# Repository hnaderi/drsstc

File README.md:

# DRSSTC

This is a work in progress...

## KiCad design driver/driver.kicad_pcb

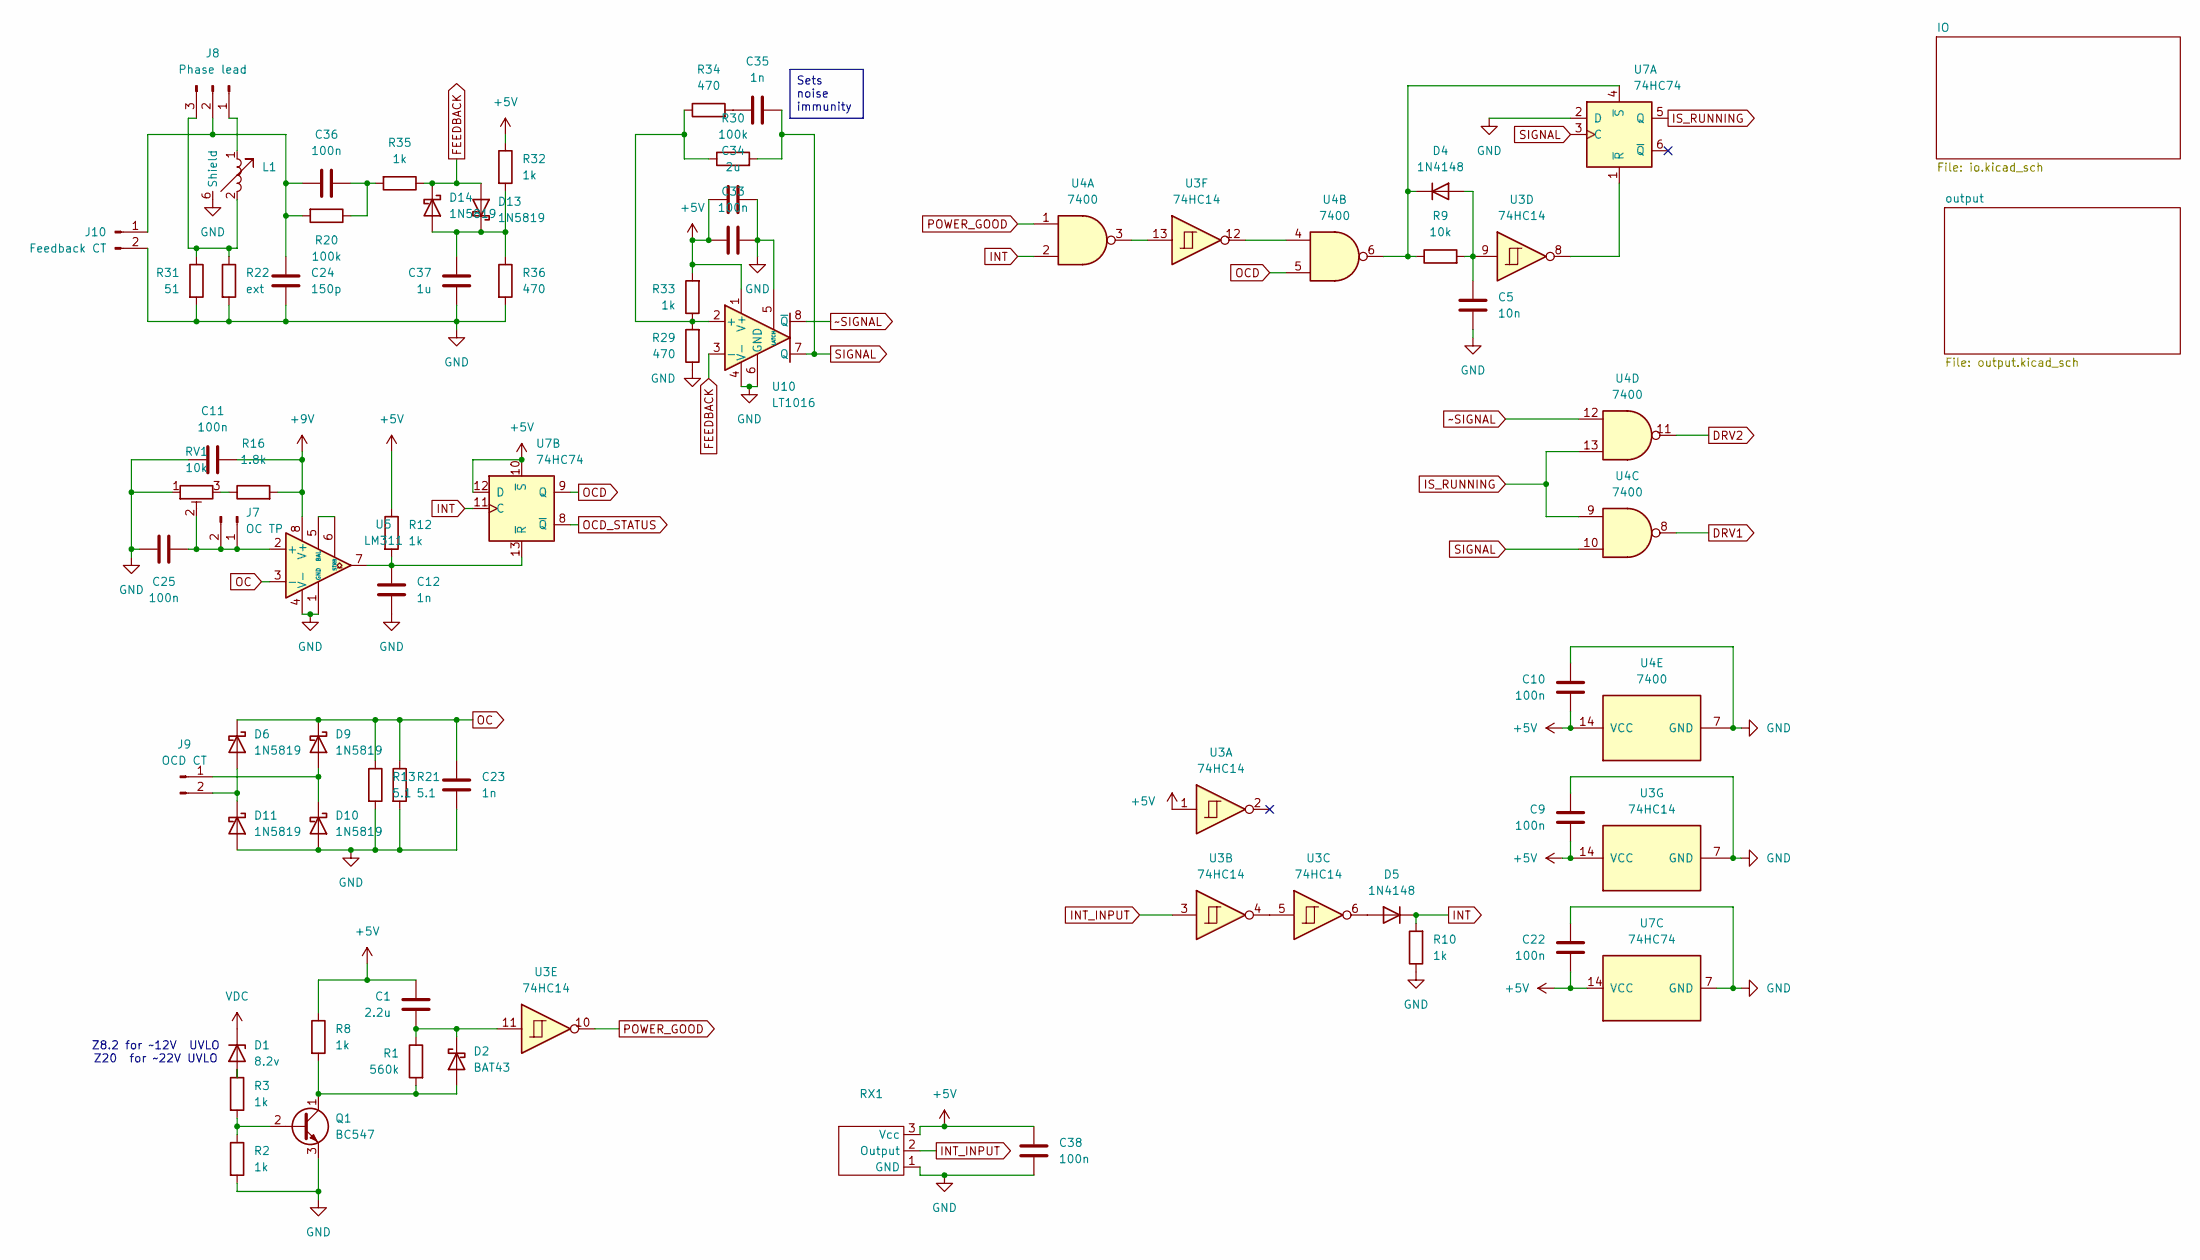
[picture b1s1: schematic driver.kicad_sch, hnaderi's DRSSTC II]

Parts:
C1: 2.2u; C_Disc_D4.7mm_W2.5mm_P5.00mm
C5: 10n; C_Disc_D4.7mm_W2.5mm_P5.00mm
C9, C10, C11, C22, C25, C33, C36, C38: 100n; C_Disc_D4.7mm_W2.5mm_P5.00mm
C12, C23, C35: 1n; C_Disc_D4.7mm_W2.5mm_P5.00mm
C24: 150p; C_Disc_D4.7mm_W2.5mm_P5.00mm
C34: 2u; C_Rect_L7.2mm_W7.2mm_P5.00mm_FKS2_FKP2_MKS2_MKP2
C37: 1u; C_Disc_D4.7mm_W2.5mm_P5.00mm
D1: 8.2v; D_DO-35_SOD27_P2.54mm_Vertical_KathodeUp
D2: BAT43; D_DO-35_SOD27_P2.54mm_Vertical_KathodeUp
D4, D5: 1N4148; D_DO-35_SOD27_P2.54mm_Vertical_KathodeUp
D6, D9, D10, D11, D13, D14: 1N5819; D_DO-41_SOD81_P2.54mm_Vertical_KathodeUp
J7: OC TP; PinHeader_1x02_P2.54mm_Vertical
J8: Phase lead; PinHeader_1x03_P2.54mm_Vertical
J9: OCD CT; JST_XH_B2B-XH-A_1x02_P2.50mm_Vertical
J10: Feedback CT; JST_XH_B2B-XH-A_1x02_P2.50mm_Vertical
L1: universal tunable inductor
Q1: BC547; TO-92_Inline_Wide
R1: 560k; R_Axial_DIN0207_L6.3mm_D2.5mm_P2.54mm_Vertical
R2, R3, R8, R10, R12, R32, R33: 1k; R_Axial_DIN0207_L6.3mm_D2.5mm_P2.54mm_Vertical
R9: 10k; R_Axial_DIN0207_L6.3mm_D2.5mm_P2.54mm_Vertical
R13, R21: 5.1; R_Axial_DIN0207_L6.3mm_D2.5mm_P2.54mm_Vertical
R16: 1.8k; R_Axial_DIN0207_L6.3mm_D2.5mm_P2.54mm_Vertical
R20: 100k; R_Axial_DIN0309_L9.0mm_D3.2mm_P2.54mm_Vertical
R22: ext; R_Axial_DIN0309_L9.0mm_D3.2mm_P2.54mm_Vertical
R29, R34, R36: 470; R_Axial_DIN0207_L6.3mm_D2.5mm_P2.54mm_Vertical
R30: 100k; R_Axial_DIN0207_L6.3mm_D2.5mm_P2.54mm_Vertical
R31: 51; R_Axial_DIN0309_L9.0mm_D3.2mm_P2.54mm_Vertical
R35: 1k; R_Axial_DIN0309_L9.0mm_D3.2mm_P2.54mm_Vertical
RV1: 10k; Potentiometer_Bourns_3296W_Vertical
RX1: hnaderi-opl530-rx
U3: 74HC14; DIP-14_W7.62mm
U4: 7400; DIP-14_W7.62mm
U5: LM311; DIP-8_W7.62mm
U7: 74HC74; DIP-14_W7.62mm
U10: LT1016; DIP-8_W7.62mm

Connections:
+5V: C1.2, C9.2, C10.2, C22.2, C33.2, C34.2, C38.1, R8.1, R12.1, R32.1, R33.2, RX1.3 (Vcc), U3.1, U3.14 (VCC), U4.14 (VCC), U7.10 (~S), U7.12 (D), U7.14 (VCC), U10.1 (V+); also elsewhere on the board
+9V: C11.2, R16.2, U5.8 (V+); also elsewhere on the board
DRV1: U4.8; also elsewhere on the board
DRV2: U4.11; also elsewhere on the board
FEEDBACK: D13.2 (A), D14.1 (K), R35.1, U10.3 (-); also elsewhere on the board
GND: C5.2, C9.1, C10.1, C11.1, C12.2, C22.1, C23.2, C24.1, C25.1, C33.1, C34.1, C37.2, C38.2, D10.2 (A), D11.2 (A), J10.2, L1.6 (Shield), Q1.3 (E), R2.2, R10.1, R13.2, R21.2, R22.2, R29.1, R31.2, R36.2, RV1.1, RX1.1 (GND), U3.7 (GND), U4.7 (GND), U5.1 (GND), U5.4 (V-), U7.2 (D), U7.7 (GND), U10.4 (V-), U10.5 (LATCH), U10.6 (GND); also elsewhere on the board
INT: D5.1 (K), R10.2, U4.2, U7.11 (C); also elsewhere on the board
INT_INPUT: RX1.2 (Output), U3.3; also elsewhere on the board
IS_RUNNING: U4.9, U4.13, U7.5 (Q)
unnamed: C35.2, R34.2
unnamed: C36.1, R20.1, R35.2
unnamed: D1.2 (A), R3.1
unnamed: D2.2 (A), Q1.1 (C), R1.2, R8.2
unnamed: C1.1, D2.1 (K), R1.1, U3.11
unnamed: C5.1, D4.2 (A), R9.2, U3.9
unnamed: D4.1 (K), R9.1, U4.6, U7.4 (~S)
unnamed: D5.2 (A), U3.6
unnamed: D9.2 (A), D10.1 (K), J9.1
unnamed: D6.2 (A), D11.1 (K), J9.2
unnamed: C37.1, D13.1 (K), D14.2 (A), R32.2, R36.1
unnamed: C25.2, J7.1, J7.2, RV1.2, U5.2 (+)
unnamed: J8.1, L1.1
unnamed: J8.3, L1.2, R22.1, R31.1
unnamed: C24.2, C36.2, J8.2, J10.1, R20.2
unnamed: Q1.2 (B), R2.1, R3.2
unnamed: R16.1, RV1.3
unnamed: U3.4, U3.5
unnamed: U3.12, U4.4
unnamed: U3.13, U4.3
unnamed: U5.5 (BAL), U5.6 (STRB)
unnamed: U3.8, U7.1 (~R)
unnamed: C12.1, R12.2, U5.7, U7.13 (~R)
unnamed: R29.2, R30.1, R33.1, R34.1, U10.2 (+)
OC: C23.1, D6.1 (K), D9.1 (K), R13.1, R21.1, U5.3 (-)
OCD: U4.5, U7.9 (Q)
OCD_STATUS: U7.8 (~Q); also elsewhere on the board
POWER_GOOD: U3.10, U4.1; also elsewhere on the board
SIGNAL: C35.1, R30.2, U4.10, U7.3 (C), U10.7 (Q); also elsewhere on the board
VDC: D1.1 (K); also elsewhere on the board
~SIGNAL: U4.12, U10.8 (~Q)

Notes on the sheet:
Z8.2 for ~12V UVLO Z20 for ~22V UVLO
Sets noise immunity

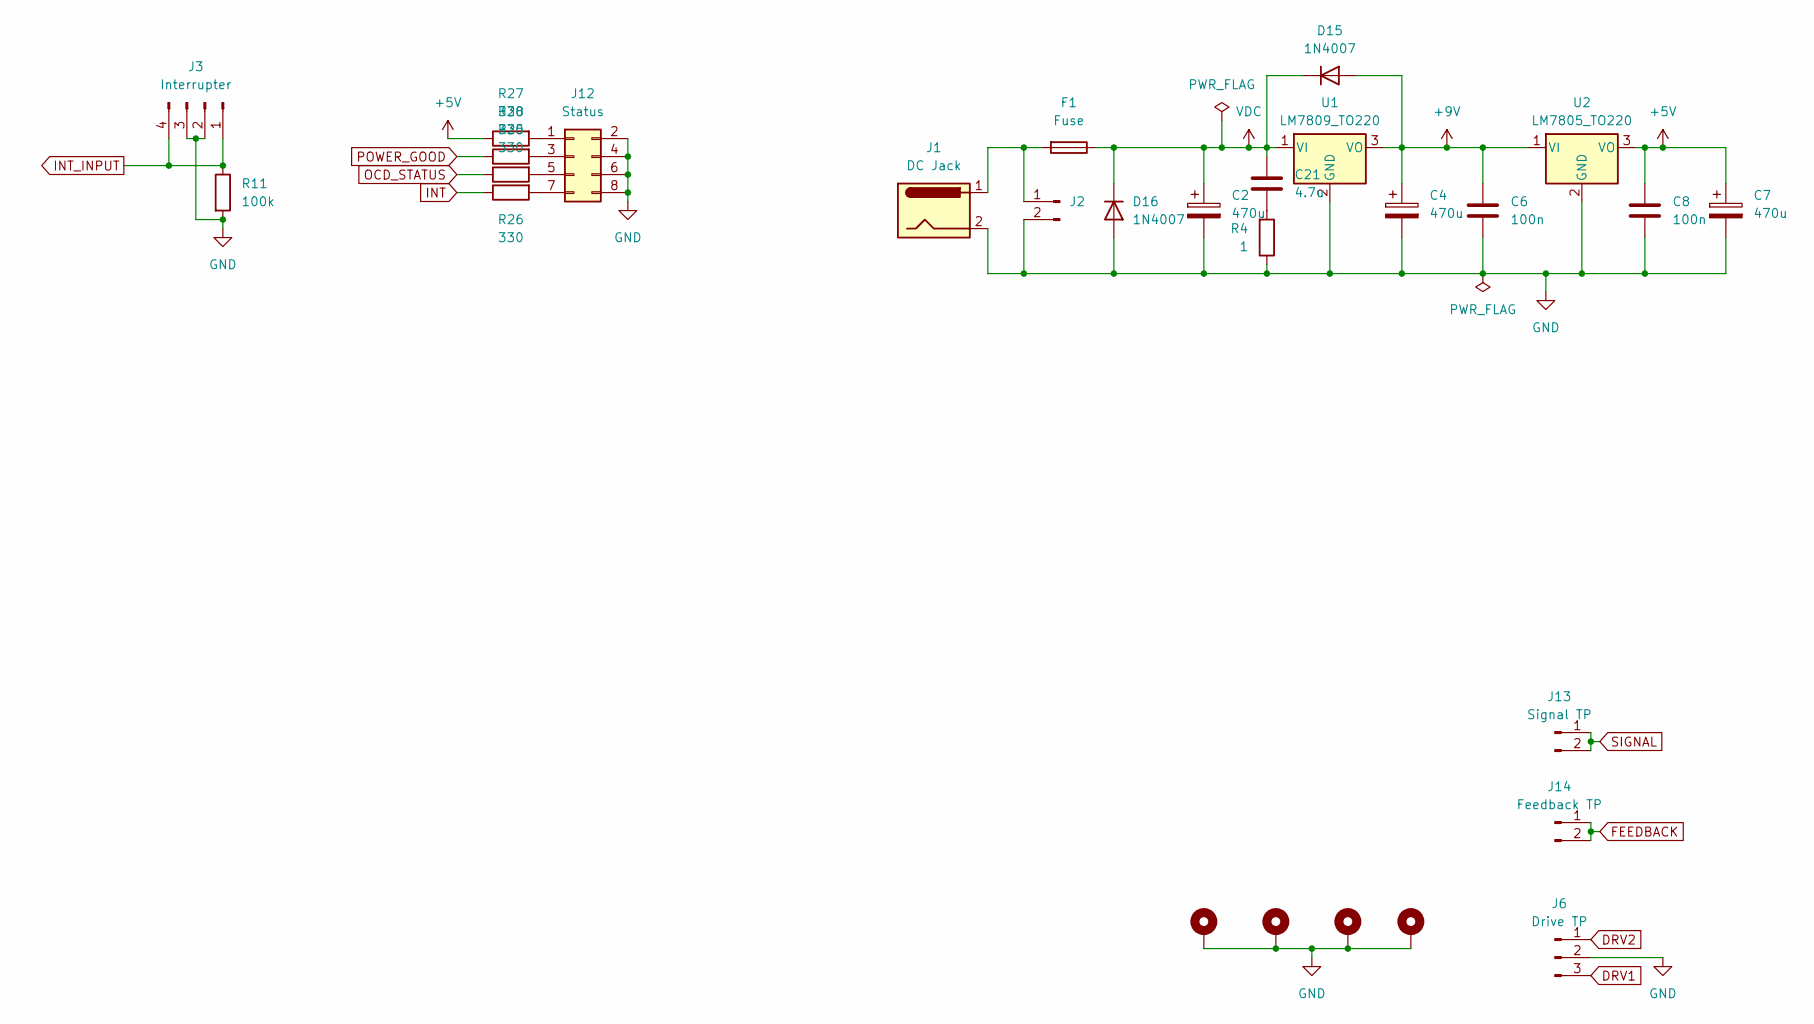
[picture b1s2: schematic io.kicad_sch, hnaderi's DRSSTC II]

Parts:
C2, C4, C7: 470u; CP_Radial_D10.0mm_P5.00mm
C6, C8: 100n; C_Disc_D4.7mm_W2.5mm_P5.00mm
C21: 4.7u; C_Disc_D4.7mm_W2.5mm_P5.00mm
D15, D16: 1N4007; D_DO-35_SOD27_P2.54mm_Vertical_KathodeUp
F1: Fuse; Fuse_Littelfuse_395Series
H1, H2, H3, H4: Body; MountingHole_3.2mm_M3_DIN965_Pad_TopBottom
J1: DC Jack; BarrelJack_Horizontal
J2: JST_XH_B2B-XH-A_1x02_P2.50mm_Vertical
J3: Interrupter; PinHeader_1x04_P2.54mm_Vertical
J6: Drive TP; PinHeader_1x03_P2.54mm_Vertical
J12: Status; PinHeader_2x04_P2.54mm_Vertical
J13: Signal TP; PinHeader_1x02_P2.54mm_Vertical
J14: Feedback TP; PinHeader_1x02_P2.54mm_Vertical
R4: 1; R_Axial_DIN0207_L6.3mm_D2.5mm_P2.54mm_Vertical
R11: 100k; R_Axial_DIN0207_L6.3mm_D2.5mm_P2.54mm_Vertical
R25, R26, R27, R28: 330; R_Axial_DIN0207_L6.3mm_D2.5mm_P2.54mm_Vertical
U1: LM7809_TO220; TO-220-3_Vertical
U2: LM7805_TO220; TO-220-3_Vertical

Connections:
+5V: C7.1, C8.1, R27.1, U2.3 (VO); also elsewhere on the board
+9V: C4.1, C6.1, D15.2 (A), U1.3 (VO), U2.1 (VI); also elsewhere on the board
DRV1: J6.3; also elsewhere on the board
DRV2: J6.1; also elsewhere on the board
FEEDBACK: J14.1, J14.2; also elsewhere on the board
GND: C2.2, C4.2, C6.2, C7.2, C8.2, D16.2 (A), H1.1, H2.1, H3.1, H4.1, J1.2, J2.2, J3.2, J3.3, J6.2, J12.2, J12.4, J12.6, J12.8, R4.1, R11.2, U1.2 (GND), U2.2 (GND); also elsewhere on the board
INT: R26.1; also elsewhere on the board
INT_INPUT: J3.1, J3.4, R11.1; also elsewhere on the board
unnamed: C21.2, R4.2
unnamed: F1.2, J1.1, J2.1
unnamed: J12.1, R27.2
unnamed: J12.3, R28.2
unnamed: J12.5, R25.2
unnamed: J12.7, R26.2
OCD_STATUS: R25.1; also elsewhere on the board
POWER_GOOD: R28.1; also elsewhere on the board
SIGNAL: J13.1, J13.2; also elsewhere on the board
VDC: C2.1, C21.1, D15.1 (K), D16.1 (K), F1.1, U1.1 (VI); also elsewhere on the board

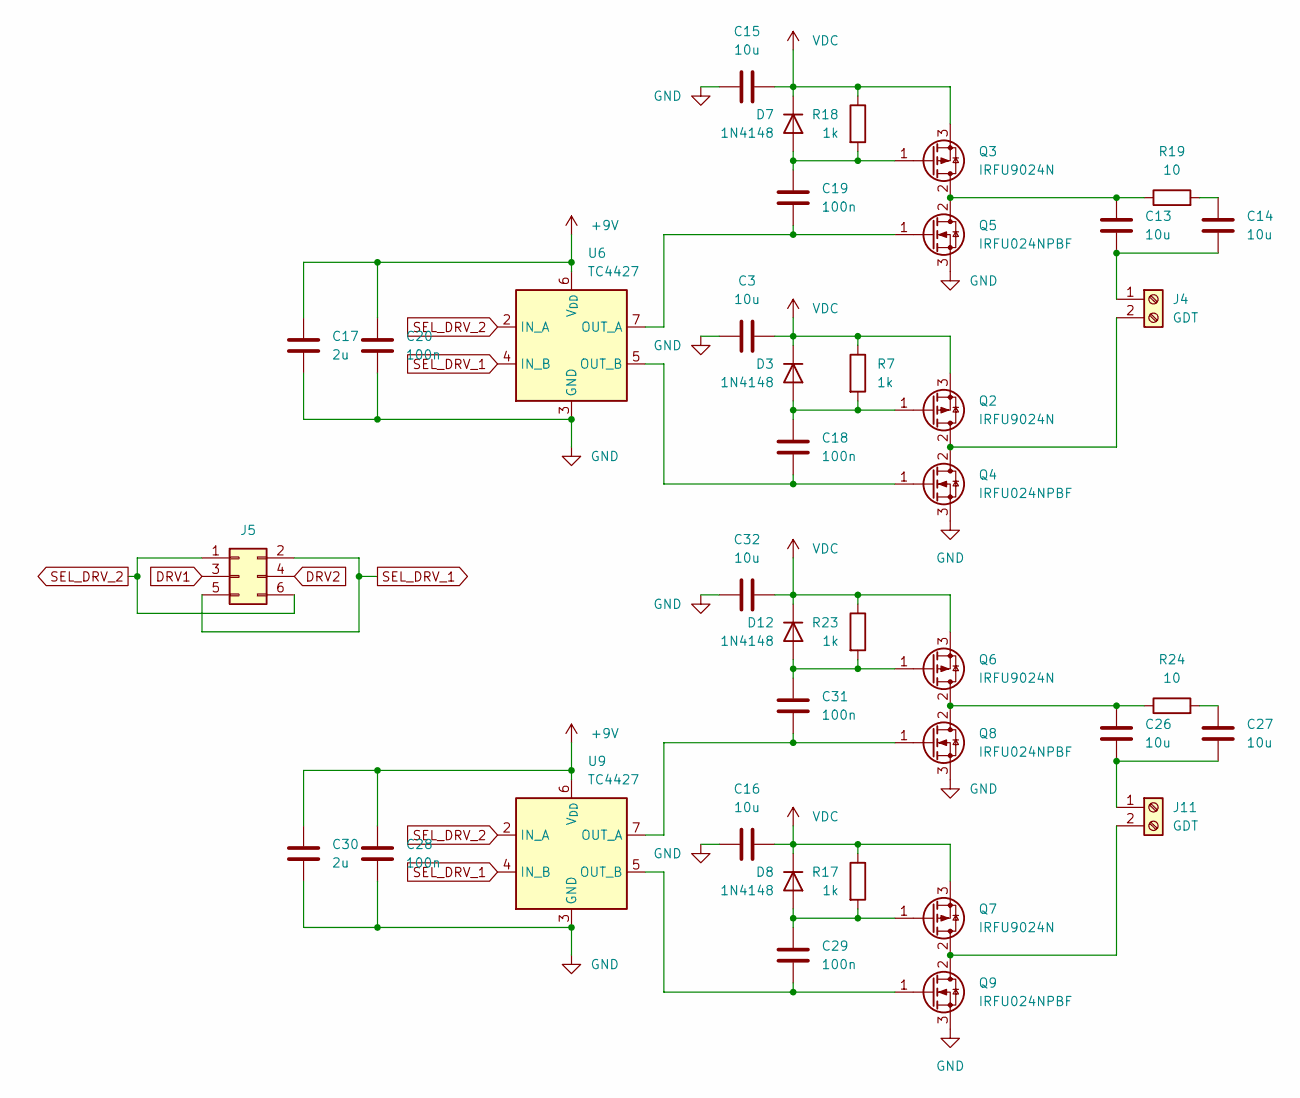
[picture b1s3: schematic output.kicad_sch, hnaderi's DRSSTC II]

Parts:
C3, C13, C14, C15, C16, C26, C27, C32: 10u; C_Disc_D4.7mm_W2.5mm_P5.00mm
C17, C30: 2u; C_Rect_L7.2mm_W7.2mm_P5.00mm_FKS2_FKP2_MKS2_MKP2
C18, C19, C20, C28, C29, C31: 100n; C_Disc_D4.7mm_W2.5mm_P5.00mm
D3, D7, D8, D12: 1N4148; D_DO-35_SOD27_P2.54mm_Vertical_KathodeUp
J4, J11: GDT; JST_XH_B2B-XH-A_1x02_P2.50mm_Vertical
J5: Conn_02x03_Odd_Even; PinHeader_2x03_P2.54mm_Vertical
Q2, Q3, Q6, Q7: IRFU9024N; TO-251-3-1EP_Horizontal_TabDown
Q4, Q5, Q8, Q9: IRFU024NPBF; TO-251-3-1EP_Horizontal_TabDown
R7, R17, R18, R23: 1k; R_Axial_DIN0207_L6.3mm_D2.5mm_P2.54mm_Vertical
R19, R24: 10; R_Axial_DIN0309_L9.0mm_D3.2mm_P2.54mm_Vertical
U6, U9: TC4427; DIP-8_W7.62mm

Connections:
+9V: C17.2, C20.2, C28.2, C30.2, U6.6 (V_{DD}), U9.6 (V_{DD}); also elsewhere on the board
DRV1: J5.3; also elsewhere on the board
DRV2: J5.4; also elsewhere on the board
GND: C3.2, C15.2, C16.2, C17.1, C20.1, C28.1, C30.1, C32.2, Q4.3 (S), Q5.3 (S), Q8.3 (S), Q9.3 (S), U6.3 (GND), U9.3 (GND); also elsewhere on the board
unnamed: C14.1, R19.2
unnamed: C27.1, R24.2
unnamed: C18.1, D3.2 (A), Q2.1 (G), R7.2
unnamed: C19.1, D7.2 (A), Q3.1 (G), R18.2
unnamed: C29.1, D8.2 (A), Q7.1 (G), R17.2
unnamed: C31.1, D12.2 (A), Q6.1 (G), R23.2
unnamed: C13.2, C14.2, J4.1
unnamed: J4.2, Q2.2 (D), Q4.2 (D)
unnamed: C26.2, C27.2, J11.1
unnamed: J11.2, Q7.2 (D), Q9.2 (D)
unnamed: C13.1, Q3.2 (D), Q5.2 (D), R19.1
unnamed: C18.2, Q4.1 (G), U6.5 (OUT_B)
unnamed: C19.2, Q5.1 (G), U6.7 (OUT_A)
unnamed: C26.1, Q6.2 (D), Q8.2 (D), R24.1
unnamed: C31.2, Q8.1 (G), U9.7 (OUT_A)
unnamed: C29.2, Q9.1 (G), U9.5 (OUT_B)
SEL_DRV_1: J5.2, J5.5, U6.4 (IN_B), U9.4 (IN_B)
SEL_DRV_2: J5.1, J5.6, U6.2 (IN_A), U9.2 (IN_A)
VDC: C3.1, C15.1, C16.1, C32.1, D3.1 (K), D7.1 (K), D8.1 (K), D12.1 (K), Q2.3 (S), Q3.3 (S), Q6.3 (S), Q7.3 (S), R7.1, R17.1, R18.1, R23.1; also elsewhere on the board

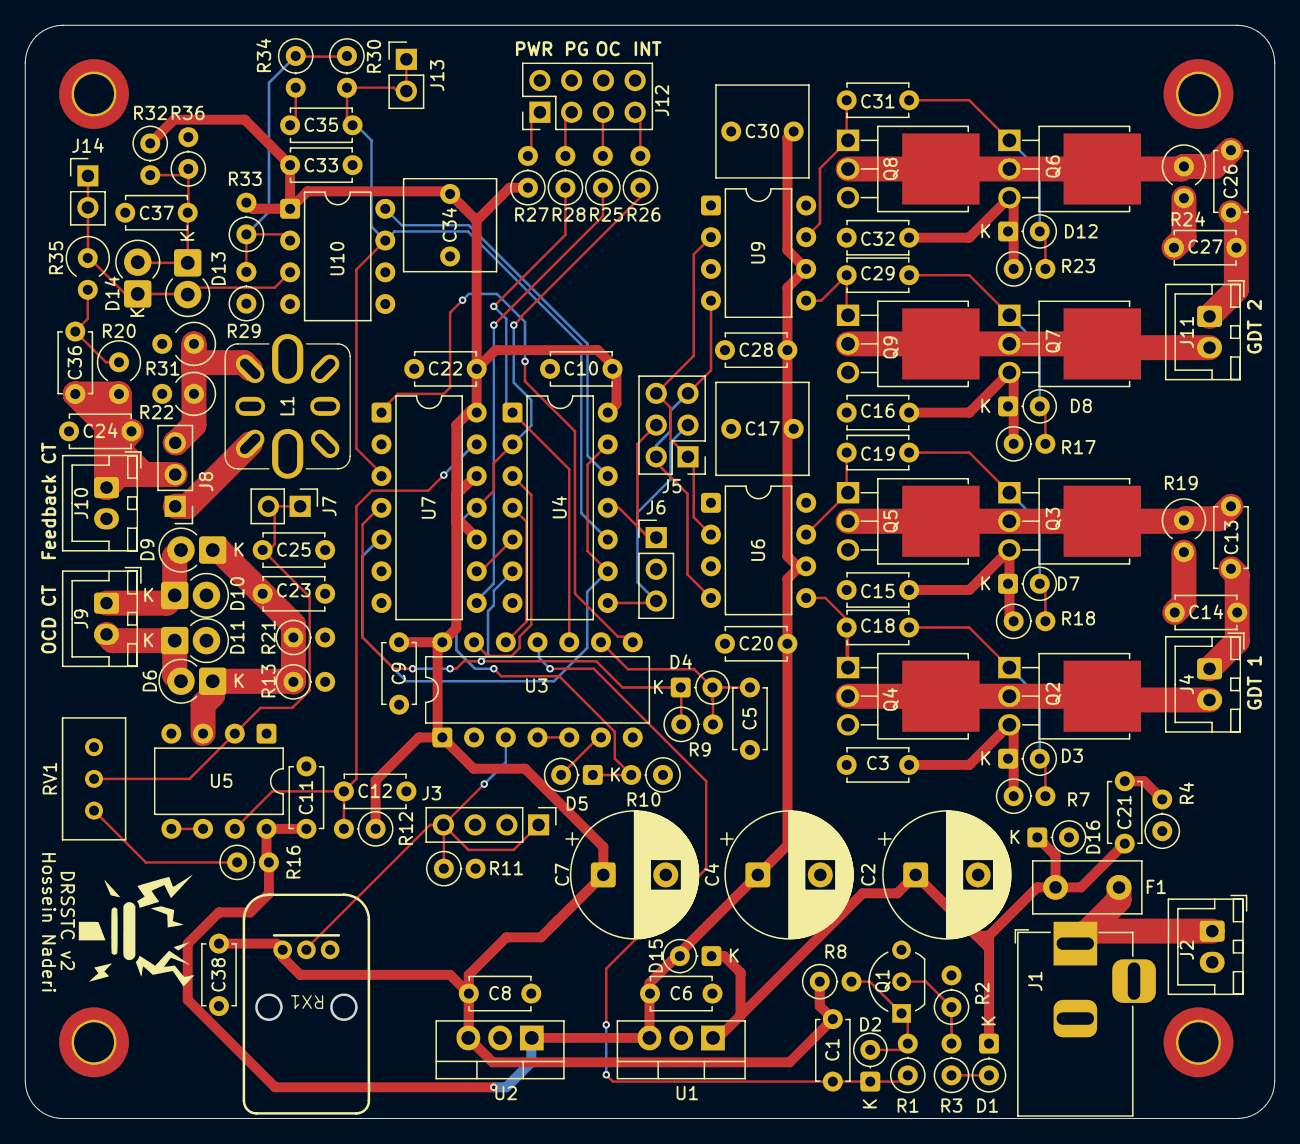
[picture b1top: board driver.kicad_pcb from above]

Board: 2 copper layers, 100.0 x 87.5 mm, 126 parts (0 on the bottom side), 64 nets.

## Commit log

2025-07-23 Added README
2025-07-24 Toslink connector parts
2025-07-24 Adjusted toslink connector parts
2025-07-24 Added footprint for toslink rx module
2025-07-29 WIP: PCB layout
2025-07-30 Fixed wrong receiver diode pins
2025-08-03 PCB draft
2025-08-11 WIP: PCB tracing
2025-08-14 Routed most of the remaining traces
2025-08-14 Duplicated GDT driver
2025-08-15 First completed revision
2025-08-16 Reannotated PCB
2025-08-16 Added fuse and more decoupling
2025-08-17 Added pull down resistor on interrupt
2025-08-17 Renamed to drsstc-v1
2025-08-17 Added opamp phase lead simulation
2025-08-17 Export fabrication outputs
2025-10-03 Added secondary cap
2026-01-07 Added my large drsstc parts
2026-01-24 Fixed missing start up pulse
2026-01-24 Renamed drsstc-v2 to driver
2026-01-24 Added javatc coils
2026-04-13 Latest working fiber connector part
2026-05-05 Added mini drsstc coil spec
2026-05-05 Renamed coils, removed test coils
2026-05-05 Added gallery
2026-05-05 Added Oscilloscope screenshot during tuning
